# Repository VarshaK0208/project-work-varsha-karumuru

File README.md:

# project-work-varsha-karumuru
# Bioreactor Electrical System Work
# Oregon State University Bioreactor Club

# 1) Project 1:
Design a Printed Circuit Board (PCB) using KiCad to combine control systems for four sensors, motors, and
pumps, ensuring power distribution for bioreactor operations.

# 2) Project 2:
Helped develop a Python-based graphical user interface (GUI) using Tkinter to provide sensor monitoring and
system control, working alongside peer engineers to synchronize software with hardware.

# Skills:
Software & Tools: KiCad (PCB Design), Git, Github, Python, Tkinter

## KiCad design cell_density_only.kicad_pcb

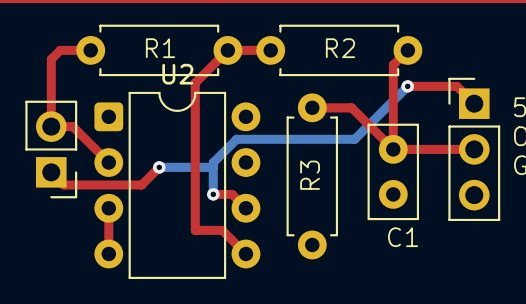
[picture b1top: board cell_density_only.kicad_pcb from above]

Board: 2 copper layers, 7 parts (0 on the bottom side), 5 nets.

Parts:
C3: .1u; C_Disc_D5.0mm_W2.5mm_P2.50mm
J1: Photodiode; PinHeader_1x02_P2.54mm_Vertical
J2: Conn_01x03; PinHeader_1x03_P2.54mm_Vertical
R1: 90; R_Axial_DIN0207_L6.3mm_D2.5mm_P7.62mm_Horizontal
R2: 2k; R_Axial_DIN0207_L6.3mm_D2.5mm_P7.62mm_Horizontal
R3: 1MEG; R_Axial_DIN0207_L6.3mm_D2.5mm_P7.62mm_Horizontal
U2: DIP-8_W7.62mm

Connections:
5V: J1.1, U2.6 (V+)
CellDensity: C3.1, R2.2, R3.1
GND: C3.2, J2.3, R3.2, U2.3 (+), U2.4 (V-)
unnamed: J1.2, R1.1, U2.2 (-)
unnamed: R1.2, R2.1, U2.5

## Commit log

2026-04-24 Project details
    Added project descriptions and skills to README.
2026-04-24 Project details!
2026-04-24 Cell Density Sensor PCB
2026-04-24 Cell Density Sensor Program File
2026-04-24 Sensor Schematic
2026-04-24 Add GUI for user to input biological recipe
2026-04-24 Rename Bioreactor_guidesign_flowchart.pdf to Project 2/GUI Design Flowchart & Logic Design
2026-04-24 Add code to send sensor and controller data over serial
2026-04-24 Rename vessel_view.py to Project 2/Code to control bioreactor vessels
2026-04-24 Rename Code to send sensor and controller data over serial monitor to Project 2/Code to send sensor and controller data over serial monitor
